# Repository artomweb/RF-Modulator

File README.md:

# RF Modulator

This is a KiCad board for the UHF TV Modulator described in a [1977 magazine article](https://ia601702.us.archive.org/19/items/ElektorMagazine/Elektor%5Bnonlinear.ir%5D%201977-12_text.pdf).

The project has been documented before by [another creator](http://www.qrp.gr/tvmod/index.htm) with a home etched PCB.

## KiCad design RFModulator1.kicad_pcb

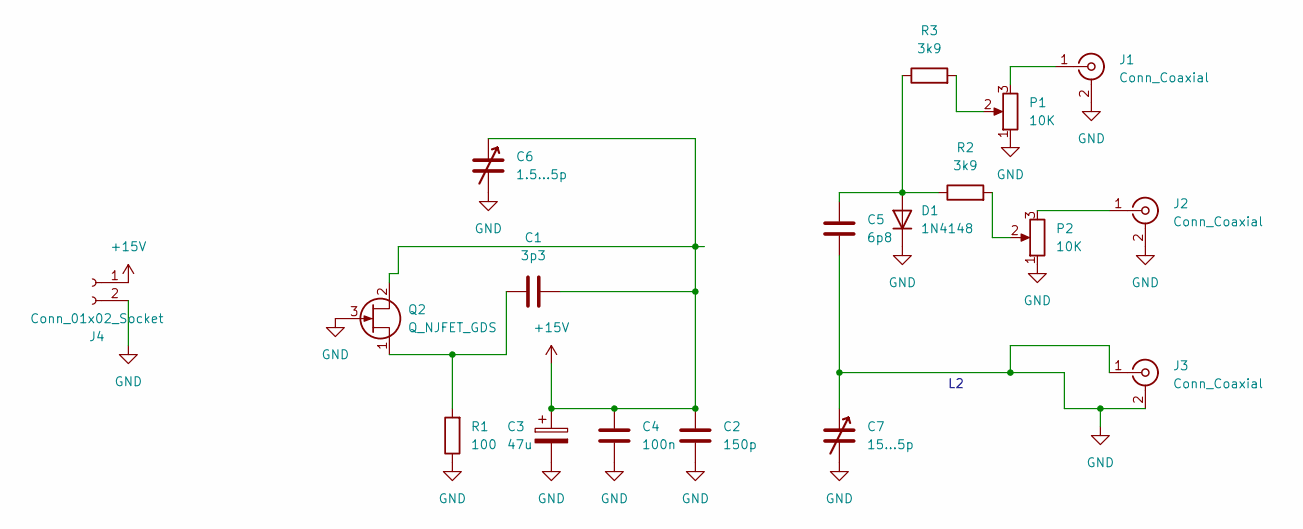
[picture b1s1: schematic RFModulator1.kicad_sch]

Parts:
C1: 3p3; C_Disc_D4.3mm_W1.9mm_P5.00mm
C2: 150p; C_Disc_D5.0mm_W2.5mm_P5.00mm
C3: 47u; C_Axial_L5.1mm_D3.1mm_P15.00mm_Horizontal
C4: 100n; C_Axial_L5.1mm_D3.1mm_P7.50mm_Horizontal
C5: 6p8; C_Disc_D5.0mm_W2.5mm_P5.00mm
C6: 1.5...5p; GXA5R000
C7: 15...5p; GXA5R000
D1: 1N4148; D_DO-35_SOD27_P10.16mm_Horizontal
J1, J2: Conn_Coaxial; SWITCHCRAFT_PJRAN1X1U04X
J3: Conn_Coaxial; VF330
J4: Conn_01x02_Socket; JST_XH_B2B-XH-A_1x02_P2.50mm_Vertical
P1, P2: 10K; Potentiometer_Runtron_RM-065_Vertical
Q2: Q_NJFET_GDS; TO-38-3
R1: 100; R_Axial_DIN0207_L6.3mm_D2.5mm_P13mm_Horizontal_copy
R2, R3: 3k9; R_Axial_DIN0207_L6.3mm_D2.5mm_P13mm_Horizontal_copy

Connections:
+15V: C1.2, C2.1, C3.1, C4.1, C6.1, J4.1, Q2.2 (D)
GND: C2.2, C3.2, C4.2, C5.2, C6.2, C7.1, C7.2, D1.1 (K), J1.2 (Ext), J2.2 (Ext), J3.1 (In), J3.2 (Ext), J4.2, P1.1, P2.1, Q2.3 (G), R1.1
unnamed: C5.1, D1.2 (A), R2.1, R3.1
unnamed: J1.1 (In), P1.3
unnamed: J2.1 (In), P2.3
unnamed: P1.2, R3.2
unnamed: P2.2, R2.2
unnamed: C1.1, Q2.1 (S), R1.2

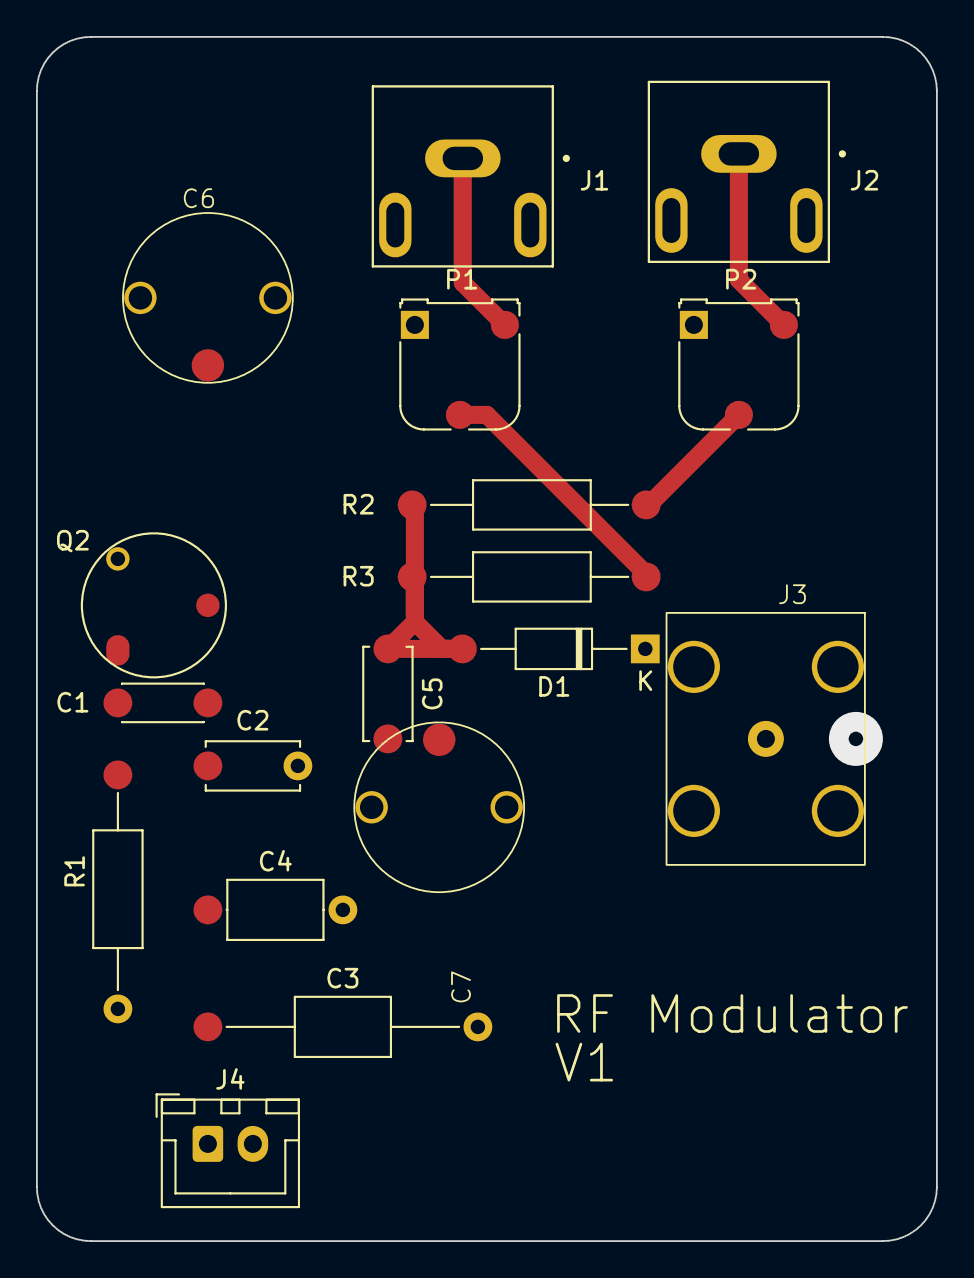
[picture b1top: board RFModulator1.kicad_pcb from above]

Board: 2 copper layers, 50.0 x 66.9 mm, 18 parts (0 on the bottom side), 8 nets.

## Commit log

2025-04-20 first2
2025-04-20 readme
2025-04-20 image to readme
2025-04-28 with jst
2025-04-28 update image
2025-05-01 Make image smaller
